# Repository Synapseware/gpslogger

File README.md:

gpslogger
=========
The GPS Logger is an meant to be a lightweight, long running GPS location recorder.  Its main goal is to periodically log GPS position data over as long a timespan as possible.  The sampling interval is kept low (usually 5 minutes) to preserve battery life.

# Background
The GPS logger uses an ATXMega A4U device (the atxmega128a4u) because it is 3.3v compliant, fast, efficient and well supported.  The 2 primary onboard devices require 3.3v for correct operation: The Adafruit Ultimate GPS v3 breakout board and an Atmel 4mb flash (an at25df321).

### Inspiration
I have created this board as a project for a friend.  You are welcome to copy the code, design, etc, as long as you retain the original author's copyright and license information.

### Folders
* /board
    - Eagle files
* /data
    - Some sample log data
* /media
    - Pictures of the board through development to final packaging
* /src
    - Project source
* /LUFA
    - LUFA library used for CDC interface

## GPS Data
(Location altered)

    $GPGGA,072450.000,4078.8163,N,10921.9609,W,1,10,1.01,104.0,M,-17.3,M,,*59
    $GPRMC,072450.000,A,4078.8163,N,10921.9609,W,0.14,355.98,170815,,,A*7A
    $GPGGA,072451.000,4078.8163,N,10921.9609,W,1,10,1.01,104.0,M,-17.3,M,,*58
    $GPRMC,072451.000,A,4078.8163,N,10921.9609,W,0.15,355.98,170815,,,A*7A
    $GPGGA,072452.000,4078.8164,N,10921.9608,W,1,10,1.01,104.0,M,-17.3,M,,*5D
    $GPRMC,072452.000,A,4078.8164,N,10921.9608,W,0.21,355.98,170815,,,A*78
    $GPGGA,072453.000,4078.8163,N,10921.9607,W,1,10,1.01,104.0,M,-17.3,M,,*54
    $GPRMC,072453.000,A,4078.8163,N,10921.9607,W,0.32,355.98,170815,,,A*73

## Rules for Saving Log Data

* Wakeup and get a fix every 5 mintues
* Stop trying to get fix data after xx seconds
    - prevent system from getting stuck without satellite data
* Each NMEA sentence is truncated to 127 bytes (+1 \0 byte)
* 2 NMEA sentences are saved to the flash together in a single page-write operation
* Fix data is parsed from GPRMC message

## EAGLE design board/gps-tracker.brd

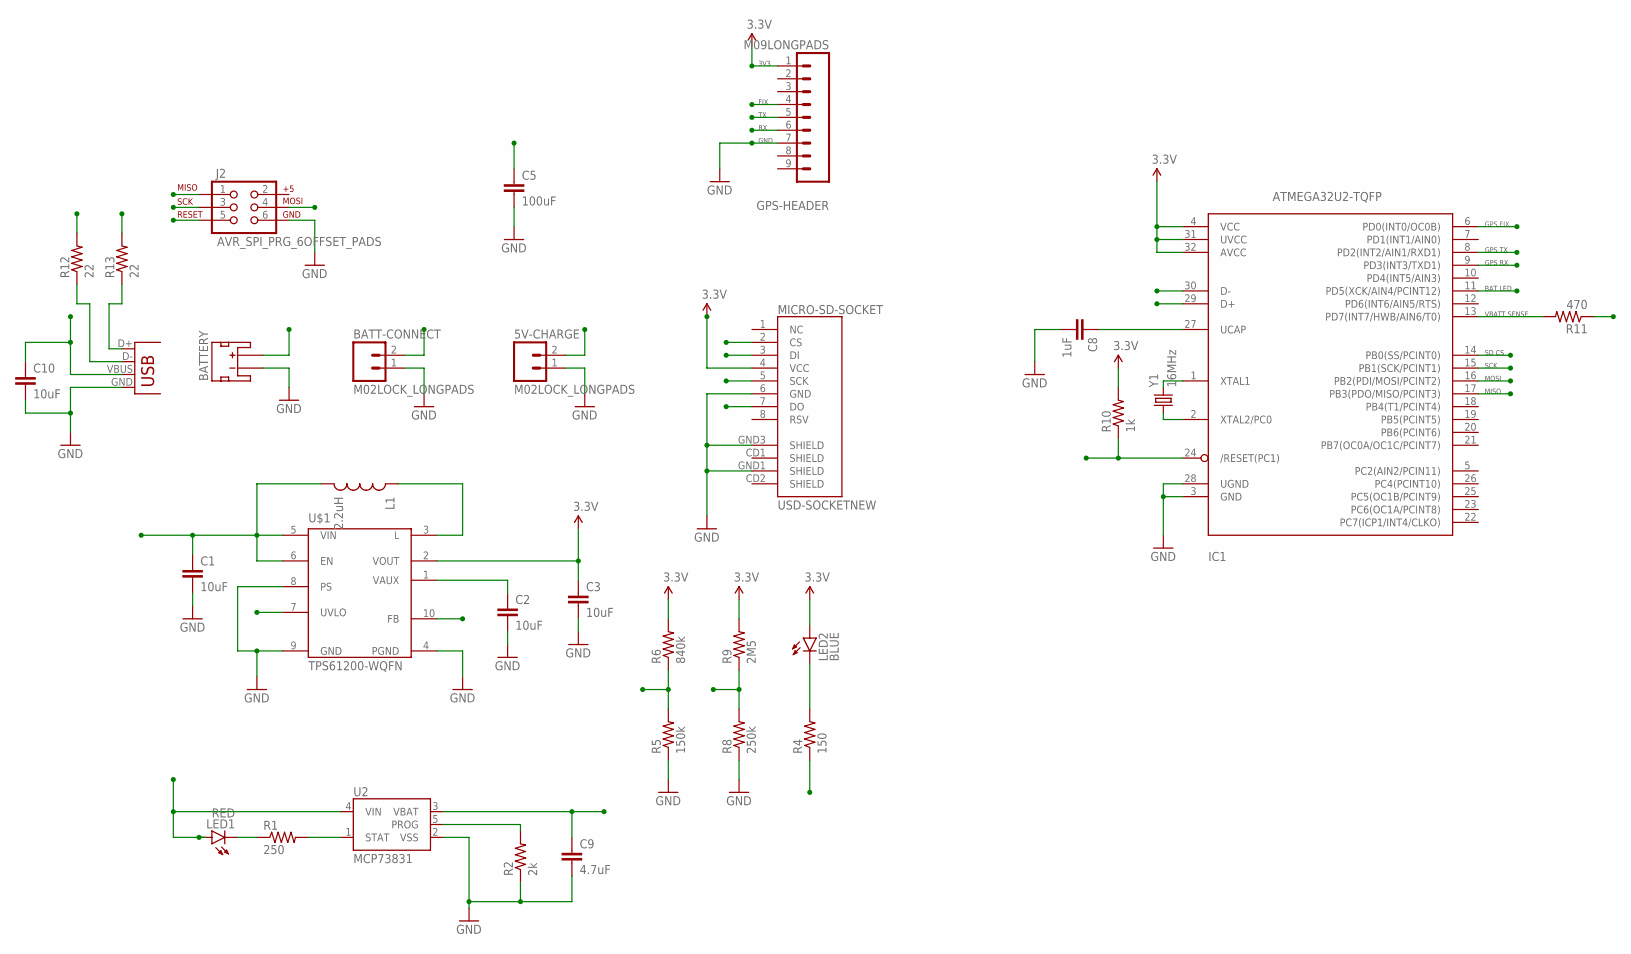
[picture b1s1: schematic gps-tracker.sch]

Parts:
5V-CHARGE: M02LOCK_LONGPADS; 1X02_LOCK_LONGPADS
BATT-CONNECT: M02LOCK_LONGPADS; 1X02_LOCK_LONGPADS
BATTERY: JST_2MM_MALE; JST-2-SMD
C1, C2, C3, C10: 10uF; 1206
C5: 100uF; 1206
C8: 1uF; 0603-CAP
C9: 4.7uF; 1206
GPS-HEADER: M09LONGPADS; 1X09_LONGPADS
IC1: ATMEGA32U2-TQFP; TQFP32-08
J2: AVR_SPI_PRG_6OFFSET_PADS; 2X3_OFFSET
L1: 2.2uH; CDRH3D28
LED1: RED; LED-0603
LED2: BLUE; LED-0603
MICRO-SD-SOCKET: USD-SOCKETNEW; MICRO-SD-SOCKET-PP
R1: 250; 0603-RES
R2: 2k; 0603-RES
R4: 150; 0805
R5: 150k; 0603-RES
R6: 840k; 0603-RES
R8: 250k; 0603-RES
R9: 2M5; 0603-RES
R10: 1k; 0805
R11: 470; 0805
R12, R13: 22; 0603-RES
U2: MCP73831; SOT23-5
U$1: TPS61200-WQFN; QFN-10
X1: USBSMD; USB-MINIB
Y1: 16MHz; CRYSTAL-SMD-5X3

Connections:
3.3V: C3.1, GPS-HEADER.1, IC1.4 (VCC), IC1.31 (UVCC), IC1.32 (AVCC), LED2.A, MICRO-SD-SOCKET.4 (VCC), R6.2, R9.2, R10.2, U$1.2 (VOUT)
/RESET: IC1.24 (/RESET(PC1)), J2.5, R10.1
BATT_LED: IC1.11 (PD5(XCK/AIN4/PCINT12)), R4.1
D+: IC1.29 (D+), R13.2
D-: IC1.30 (D-), R12.2
FB: R5.2, R6.1, U$1.10 (FB)
GND: 5V-CHARGE.1, BATT-CONNECT.1, BATTERY.1 (-), C1.2, C2.2, C3.2, C5.2, C8.2, C9.2, C10.2, GPS-HEADER.7, IC1.3 (GND), IC1.28 (UGND), J2.6, MICRO-SD-SOCKET.6 (GND), MICRO-SD-SOCKET.GND1 (SHIELD), MICRO-SD-SOCKET.GND3 (SHIELD), R2.1, R5.1, R8.1, U2.2 (VSS), U$1.4 (PGND), U$1.8 (PS), U$1.9 (GND), X1.GND
GPS_FIX: GPS-HEADER.4, IC1.6 (PD0(INT0/OC0B))
GPS_RX: GPS-HEADER.6, IC1.8 (PD2(INT2/AIN1/RXD1))
GPS_TX: GPS-HEADER.5, IC1.9 (PD3(INT3/TXD1))
MISO: IC1.17 (PB3(PDO/MISO/PCINT3)), J2.1, MICRO-SD-SOCKET.7 (DO)
MOSI: IC1.16 (PB2(PDI/MOSI/PCINT2)), J2.4, MICRO-SD-SOCKET.3 (DI)
unnamed: R1.2, U2.1 (STAT)
unnamed: L1.1, U$1.3 (L)
unnamed: LED1.C, R1.1
unnamed: C2.1, U$1.1 (VAUX)
unnamed: LED2.C, R4.2
unnamed: R2.2, U2.5 (PROG)
unnamed: IC1.13 (PD7(INT7/HWB/AIN6/T0)), R11.2
unnamed: IC1.1 (XTAL1), Y1.3 (2)
unnamed: IC1.2 (XTAL2/PC0), Y1.1
unnamed: C8.1, IC1.27 (UCAP)
unnamed: R13.1, X1.D+
unnamed: R12.1, X1.D-
SCK: IC1.15 (PB1(SCK/PCINT1)), J2.3, MICRO-SD-SOCKET.5 (SCK)
SD_CS: IC1.14 (PB0(SS/PCINT0)), MICRO-SD-SOCKET.2 (CS)
UVLO: R8.2, R9.1, U$1.7 (UVLO)
VBATT: BATT-CONNECT.2, BATTERY.2 (+), C1.1, C5.1, C9.1, L1.2, R11.1, U2.3 (VBAT), U$1.5 (VIN), U$1.6 (EN)
VUSB: 5V-CHARGE.2, C10.1, LED1.A, U2.4 (VIN), X1.VBUS

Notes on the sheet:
3V3
FIX
GND
VBATT SENSE
GPS FIX
GPS TX
GPS RX
SD CS
MOSI
MISO
SCK
BAT LED

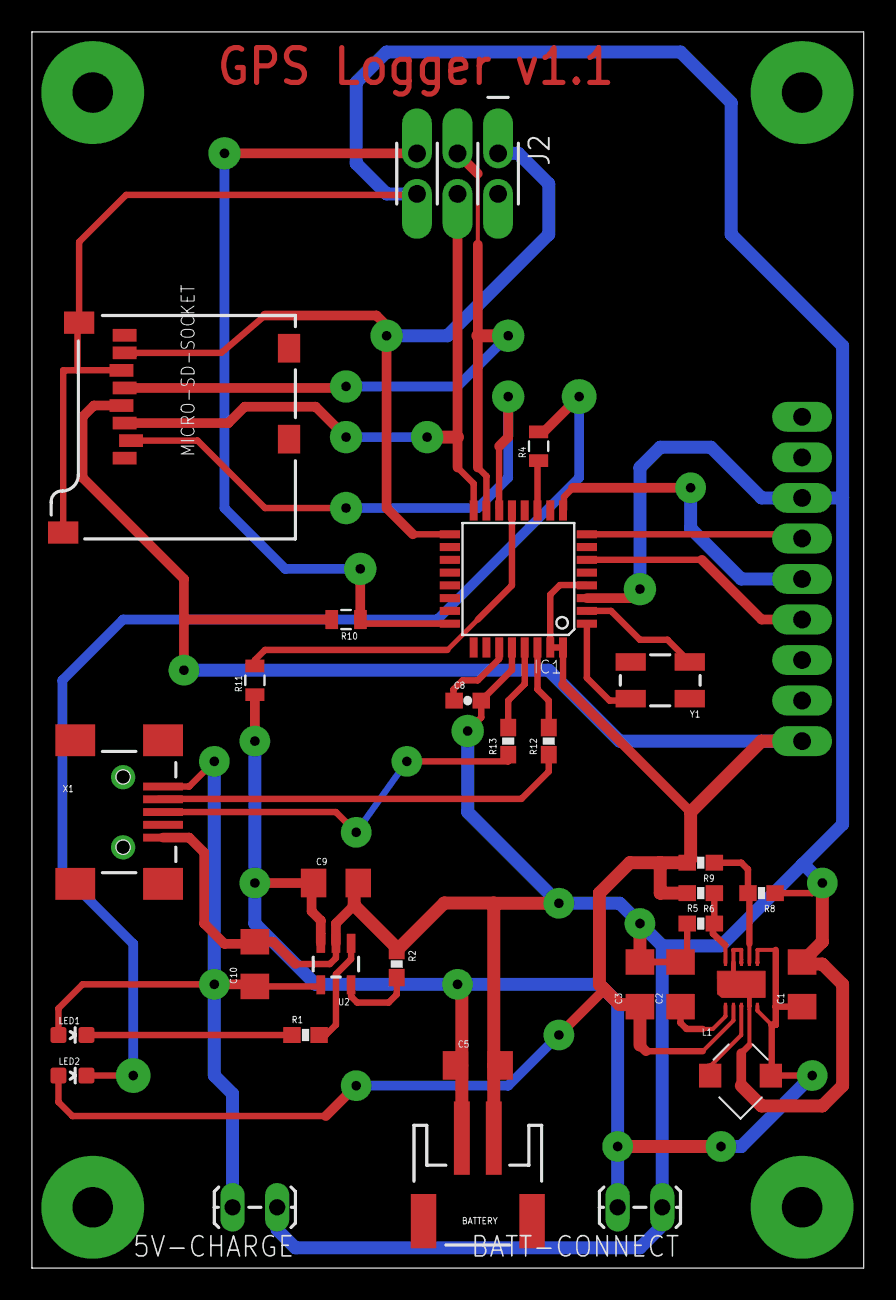
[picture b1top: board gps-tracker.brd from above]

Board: 2 copper layers, 52.1 x 77.5 mm, 32 parts (1 on the bottom side), 29 nets.

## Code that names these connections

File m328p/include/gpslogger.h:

#ifndef __GPSLOGGER__H_
#define __GPSLOGGER__H_

#include <avr/wdt.h>
#include <avr/sleep.h>
#include <avr/power.h>
#include <avr/interrupt.h>



//------------------------------------------------------------------------
// Designate pins
const int GPS_TX			= 5;
const int GPS_RX			= 6;
const int BATT_SENSE		= 0;

/*
 * GPX_FIX    2     PD2
 * GPX_TX     5     PD5
 * GPX_RX     6     PD6
 * DBG_LED    8     PB0 
 * SD_CS      10    PB2
 * BATT_SENSE n/a
*/

// We don't want to use Arduino's heavy-handed port manip code for something
// that takes only a byte or two with direct port access
#define SD_PORT         PORTB
#define SD_DDR          DDRB
#define SD_CS           PORTB2

#define DBG_LED_PORT    PORTB
#define DBG_LED_DDR     DDRB
#define DBG_LED         PORTB0

#define GPS_PORT        PORTD
#define GPS_DDR         DDRD
#define GPS_PIN         PIND
#define GPS_FIX         PORTD2

//------------------------------------------------------------------------
const uint32_t SECONDS_BETWEEN_RESETS	= 86400UL;

//------------------------------------------------------------------------
// Heartbeat delays for normal and low battery conditions
const uint16_t MILLIS_TO_BLINK			= 5;		// length of heartbeat
const uint16_t MILLIS_BETWEEN_BLINK		= 10000;	// ms delay between heartbeats
const uint16_t MILLIS_BATTERY_LOW		= 3000;		// ms delay between heartbeats
const int16_t  LOW_BATTERY				= 951;		// 3.0v


//------------------------------------------------------------------------
// number of seconds between fix-capture-record events
const uint16_t RECORDING_TIMEOUT		= (60 * 5);

// system will sleep if no fix after timeout (seconds)
const uint16_t FIX_TIMEOUT				= 120;


//------------------------------------------------------------------------
// Additional GPS module configuration strings
#define PMTK_HOT_START			"$PMTK101*32"

//#define PMTK_FULL_RESET			"$PMTK104*37"
//#define PMTK_PERIODIC_NORM		"$PMTK225,0*2B"
//#define PMTK_PERIODIC_INIT		"$PMTK225,1,60000,600000,120000,120000*16"
//#define PMTK_PERIODIC_LOCT		"$PMTK225,9*22"

// 5 minute timeout on backup mode
#define PMTK_BACKUP_MODE		"$PMTK291,7,0,300000,1*0D"

#define print_enabled

#ifdef print_enabled
	#define PRINT(x)		  Serial.print(x)
	#define PRINTLN(x)		Serial.println(x)
#else
	#define PRINT(x)
	#define PRINTLN(x)
#endif


#endif

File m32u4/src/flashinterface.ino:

/*
Hardware interface for AT25DF321:
Since the Atmega32u4 is a 5v device, a TSX0108e logic-level bi-directional translator is used.
The following ports map the SPI interface to the flash device:

32u4	Pin		Tsx		Flash	Color
-----	----	----	-----	-----
SS(CS)	PB0		7		1		Purple
SCK		PB1		5		6		Blue
MOSI	PB2		6		5		Yellow
MISO	PB3		8		2		Green


*/



uint32_t _writeAddress = 0;


uint32_t currentWriteAddress(void)
{
	return _writeAddress;
}


/** TODO:  Improve this so it does a b-search and finds the first free address within a page.  */
int32_t findFirstFreeAddress(void)
{
	Serial.println(F("Finding first free address"));
	setDbgLed();

	// Wait for device to not be busy
	if (flash->busy())
	{
		Serial.println(F("Device is busy - waiting"));
		setErrLed();

		// wait for ready state
		while (!flash->busy());
		clearErrLed();
	}

	Serial.println(F("Opening flash device for read at position 0"));
	if (!flash->open(MODE_READ, 0))
	{
		Serial.println(F("Failed to open device for reading!"));
		clearDbgLed();
		return -1;
	}

	// start checking the first byte of each page.  If the page is free, check the whole page before it.
	uint32_t address = 0;
	while (address < FLASH_TOTAL_SIZE)
	{
		//Serial.print(F("  checking byte at address ")); Serial.println(address);
		flash->seek(address);
		int data = flash->read();
		if (data == -1)
		{
			Serial.print(F("Failed reading the first byte of ")); Serial.println(address);
			setErrLed();
			clearDbgLed();
			return -1;
		}

		// If the first byte is not 0xFF, assume the page is not empty and skip to the next page
		if (data != 0xFF)
		{
			address += 256;
			continue;
		}

		// Since the first byte is not 0xFF, assume the page is not empty, and move back to the previous page
		// and begin searching for the first free byte within that page
		address -= 256;
		//Serial.print(F("  search within previous page ")); Serial.println(address);
		flash->seek(address);

		// found a page that appears to be empty, check the page before it to get the first free address
		uint8_t count = 0;
		while (++count != 0)
		{
			data = flash->read();
			if (data == 0xFF)
				break;
		}

		// found our first free address
		_writeAddress = flash->position();
		break;
	}

	//Serial.print(F("Found the first free address at ")); Serial.println(_writeAddress);
	flash->close();
	clearDbgLed();

	return _writeAddress;
}

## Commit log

2014-04-28 Initial commit of the GPS Logger to the public repo (copied from private repo)
2014-06-01 Updating readme and ignore file list
2014-06-01 Updating board to correct for previous errors, adding another status LED and bringing out the GPS EN pin to the arduino
2015-08-02 Fixing layout problems from v1
2015-08-02 Adding UVLO
2015-08-02 Adding data
2015-08-03 Initial commit of atmega32u2 conversion
2015-08-03 Working on gpslogger compilation
2015-08-03 Getting build working with MT-DB-U2
    MattairTech atmeg32u2 is an Arduino clone that this board is based off of.
2015-08-03 Adding MattairTech Arduino install
    This is the install package for the MattairTech MT-DB-U2 board, an atmega32u2 arduino clone.
2015-08-03 Updating fuses for atmega32u2
2015-08-05 Updating makefile
2015-08-05 Working on compiling under linux
2015-08-05 Working on Linux compile with new libs
2015-08-05 Compiling with new atmega32u2 lib
    Board is reasonably compiling with atmega32u2 drivers from mattairtech.
2015-08-06 Cleaning up scope issues
2015-08-07 Switched to minimus32 arduino variant
2015-08-07 Fixing timeouts. Have to fix memory issues as well.
2015-08-07 Updating docs
2015-08-16 LUFA CDC drivers for ATXMega128a4u
2015-08-16 Now building for xmega & LUFA
2015-08-16 Adding LED debug
2015-08-16 LEDs and cleanup
2015-08-16 Interrupt toggling of onboard LED at 1s intervals
2015-08-17 GPS interfacing in progress
    Can read and write to GPS serial port.
2015-08-17 Readme and cleanup
2015-08-17 Ignoring arduino build folders
2015-08-17 Adjusting LUFA path
2015-08-18 Working on SPI flash support
2015-08-18 Reading data from flash
2015-08-19 Adding console program to test c features
2015-08-20 Updating readme with GPS sample data
2015-08-20 Working on GPS parsing
2015-08-21 Improving support for GPS and FLASH
2015-08-21 Various improvements to the GPS logger
2015-08-22 CDC cleanup
2015-08-22 Refactoring at25df321 driver and initialization
    Now successfully reading from FLASH. Use port C since the SPI pins for
    port D on the MattairTech ATXMega128a4u breakout board are shared with
    the USB interface.
2015-08-24 Logging/Diag output
2015-08-24 Parsing GPRMC message for fix data
2015-08-25 Trying to get DSR signal to work
2015-08-26 Updating connect/disconnect processing
2015-08-27 Logging GPS data to the USB port
2015-08-29 Updates for smoother GPS module interaction
2015-08-30 Updates to GPS Serial and SPI flash driver
    The GPS serial commands need to be terminated with \r\n. AT25DF321
    Flash chip constants. Switching USB sync event to high-priority
    interrupt handler.
2015-08-31 Improving GPS library
2015-09-02 Begin update to maximize flash usage
2015-09-03 Flash driver is able to save
2015-09-03 Working out kinks with NMEA persistence
2015-09-07 Updating flash driver for easier use
2015-09-09 Saving GPS data to flash and logging any existing data
2015-09-09 Updating status LEDs
2015-11-10 Fixed misc. bugs with GPS logger.
2015-11-10 Improving sentence-write algorithm
2015-11-11 Misc. updates
    Problem with the board was hardware related - the flash wasn't seating
    properly in the perf board.
2015-11-11 Moved greeting code and added deep-power down
2015-11-11 Cleanup global protect/unprotect
2015-11-13 Hacking together the write problems
2015-11-16 Fixing sentence persistence
2015-11-17 Successfully writing NMEA data
    Had add pull-up resistors to SCK, MISO and MOSI (/SS could probably use
    one too but it's working OK without it for the moment).
2015-11-17 Improving logging and timeout functionality
2015-11-18 Preparing for power-save modes between logging
2015-11-18 WIP: RTC timeouts
2015-11-18 Power saving on GPS seems to be working
2015-11-18 More testing
2015-11-18 Adding test program
2015-11-18 Applying fixes
2015-11-20 Logging is now working well.
2015-11-23 Updating LUFA
2015-11-23 GPS menu for debugging
2015-11-24 Show GPS state information
2015-11-28 Adding serial receiver board
2015-11-28 Final version of DIAG board
2015-11-28 GPS logging working much better
    Fixed the GPS initialization problem.
2015-11-28 Misc stupid tests
2015-11-30 Changing messaging behavior
2015-11-30 Create blocking stream
2015-12-01 Adding port drivers from Atmel
2015-12-01 Bringing in port_driver code from Atmel.
2017-08-19 Cleanup
2017-08-21 WIP: Migrating hardware to HAL
    New HAL wrapper will simplify migrating to another platform if
    necessary.
2017-08-23 Upgrading LUFA and fixing system crash
    Board was crashing after previous changes. Upgraded LUFA and fixed
    problem with crash after a GPS capture.
2017-08-25 WIP: Trying to fix USB connection issues
    Board takes ~30 seconds to connect.
2017-08-26 USB working (finally)
    CDC mode is working reliably. There's a bug somewhere further in with
    the GPS processing, NMEA parsing, etc. that's causing the board to
    crash/not work and is especially interfering with the USB
    communications.
2017-08-27 Displaying battery voltage
    Display battery voltage using ADCA. Also, remapped GPS control pins and
    control register so the USART port and the control pins port are the
    same.
2019-12-08 WIP: Adding LCD driver
2019-12-09 Cleanup, trying to fix bug with sending commands to module
2019-12-09 Fix typo
2019-12-10 Trying to fix version and rouge reprint bugs
2019-12-15 Move original Atmega328p project to sub folder
2019-12-15 Import other boards
2019-12-15 Ignore build files in xmega project
2019-12-15 Add required libraries
2019-12-15 Update libraries
2019-12-16 Ignore DS_Store files
2019-12-17 WIP: Flash support
2019-12-17 32u4 version w/flash is compiling
2019-12-18 Updating free block search
2019-12-20 Improved flash support
2019-12-20 Adding tests
2019-12-20 Updating flash
2019-12-21 WIP: Flash "stream" support
2019-12-23 WIP: Working on flash IO
2019-12-23 WIP: Working on finding first free address in flash
2019-12-24 Able to search for first free address in ext flash
2019-12-24 Reduce logging
2019-12-24 Adding TeensyLC shell
2019-12-25 WIP: Was going to try and parse up the NMEA sentence
2019-12-25 Initial build via platformIO
2019-12-25 Add m328p original source code archive
2019-12-28 Compiles in PIO realm
2019-12-28 Compiling with PIO and code cleanup
2019-12-28 WTF. Sometimes a hard reset is required
2019-12-29 WIP: Trying to get board to work
    Various hardware problems
2019-12-29 Ignore all PIO folders
2019-12-30 Moving files, breaking up code in prep for C++
2019-12-30 Improving
2019-12-30 Hardware appears to reading out data
2019-12-31 Cleanup more files
2020-01-01 Working on CPP version
2020-01-01 CPP conversion compiles
    Don't know if it works tho :)
2020-01-01 Add arduino core files (used as examples/templates)
2020-01-01 Building, but not tested
2020-01-02 Improve free-block search

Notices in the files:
parts and their libraries:
SparkFun: Licensing: CC v3.0 Share-Alike You are welcome to use this library for commercial purposes.
